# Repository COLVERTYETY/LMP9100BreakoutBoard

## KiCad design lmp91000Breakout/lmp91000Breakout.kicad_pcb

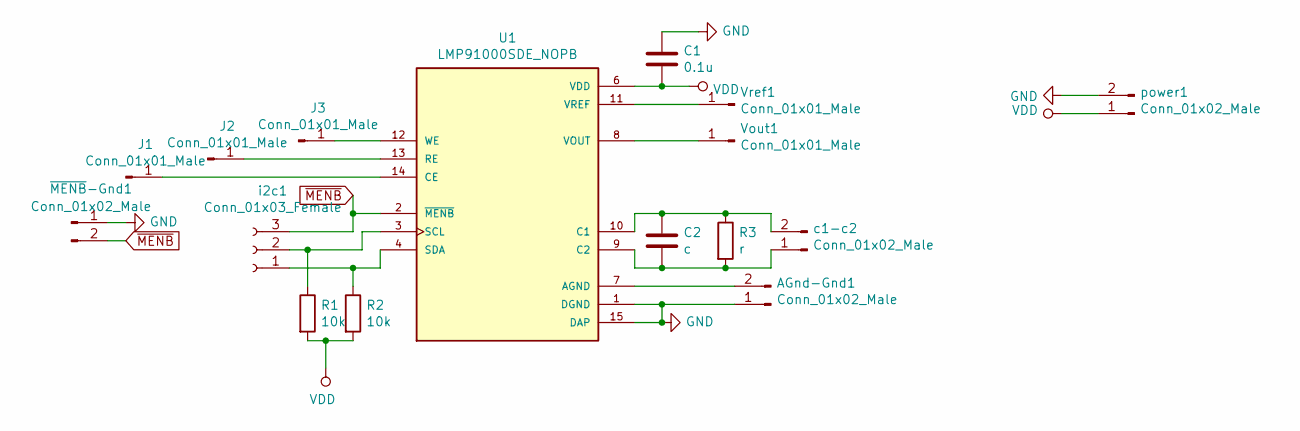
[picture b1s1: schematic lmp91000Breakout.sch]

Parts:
AGnd-Gnd1: Conn_01x02_Male; PinHeader_1x02_P2.54mm_Vertical
C1: 0.1u; C_1206_3216Metric_Pad1.42x1.75mm_HandSolder
C2: c; C_1206_3216Metric_Pad1.42x1.75mm_HandSolder
J1, J2, J3: Conn_01x01_Male; PinHeader_1x01_P2.54mm_Vertical
R1, R2: 10k; R_1206_3216Metric_Pad1.42x1.75mm_HandSolder
R3: r; R_1206_3216Metric_Pad1.42x1.75mm_HandSolder
U1: LMP91000SDE_NOPB; SON50P400X400X80-15N; PARTREV DEC 2014
Vout1: Conn_01x01_Male; PinHeader_1x01_P2.54mm_Vertical
Vref1: Conn_01x01_Male; PinHeader_1x01_P2.54mm_Vertical
c1-c2: Conn_01x02_Male; PinHeader_1x02_P2.54mm_Vertical
i2c1: Conn_01x03_Female; PinHeader_1x03_P2.54mm_Vertical
power1: Conn_01x02_Male; PinHeader_1x02_P2.54mm_Vertical
~MENB~-Gnd1: Conn_01x02_Male; PinHeader_1x02_P2.54mm_Vertical

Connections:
GND: AGnd-Gnd1.1, C1.1, U1.1 (DGND), U1.15 (DAP), power1.2, ~MENB~-Gnd1.1
unnamed: AGnd-Gnd1.2, U1.7 (AGND)
unnamed: C2.1, R3.1, U1.10 (C1), c1-c2.2
unnamed: C2.2, R3.2, U1.9 (C2), c1-c2.1
unnamed: J1.1, U1.14 (CE)
unnamed: J2.1, U1.13 (RE)
unnamed: J3.1, U1.12 (WE)
unnamed: R1.1, U1.3 (SCL), i2c1.2
unnamed: R2.1, U1.4 (SDA), i2c1.1
unnamed: U1.8 (VOUT), Vout1.1
unnamed: U1.11 (VREF), Vref1.1
VDD: C1.2, R1.2, R2.2, U1.6 (VDD), power1.1
~MENB~: U1.2 (~MENB), i2c1.3, ~MENB~-Gnd1.2

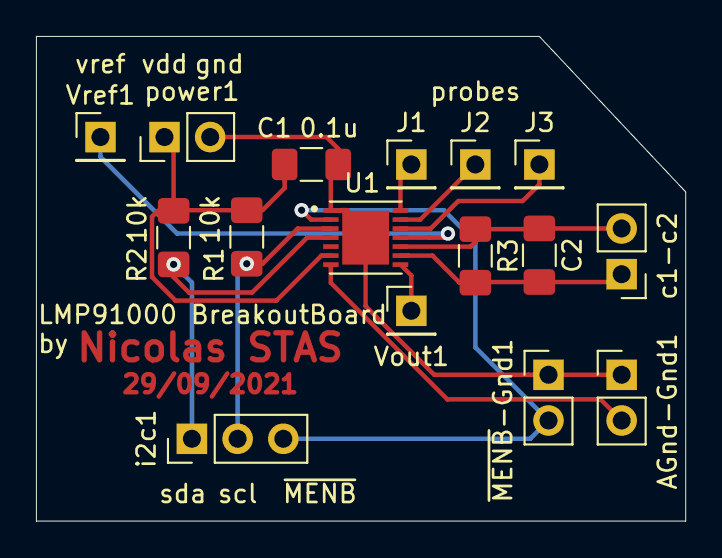
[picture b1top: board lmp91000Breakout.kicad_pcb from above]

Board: 2 copper layers, 36.1 x 26.9 mm, 15 parts (0 on the bottom side), 13 nets.

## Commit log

2021-09-29 changed stuff
2021-09-29 changed readme
2021-09-29 added Qrcode
